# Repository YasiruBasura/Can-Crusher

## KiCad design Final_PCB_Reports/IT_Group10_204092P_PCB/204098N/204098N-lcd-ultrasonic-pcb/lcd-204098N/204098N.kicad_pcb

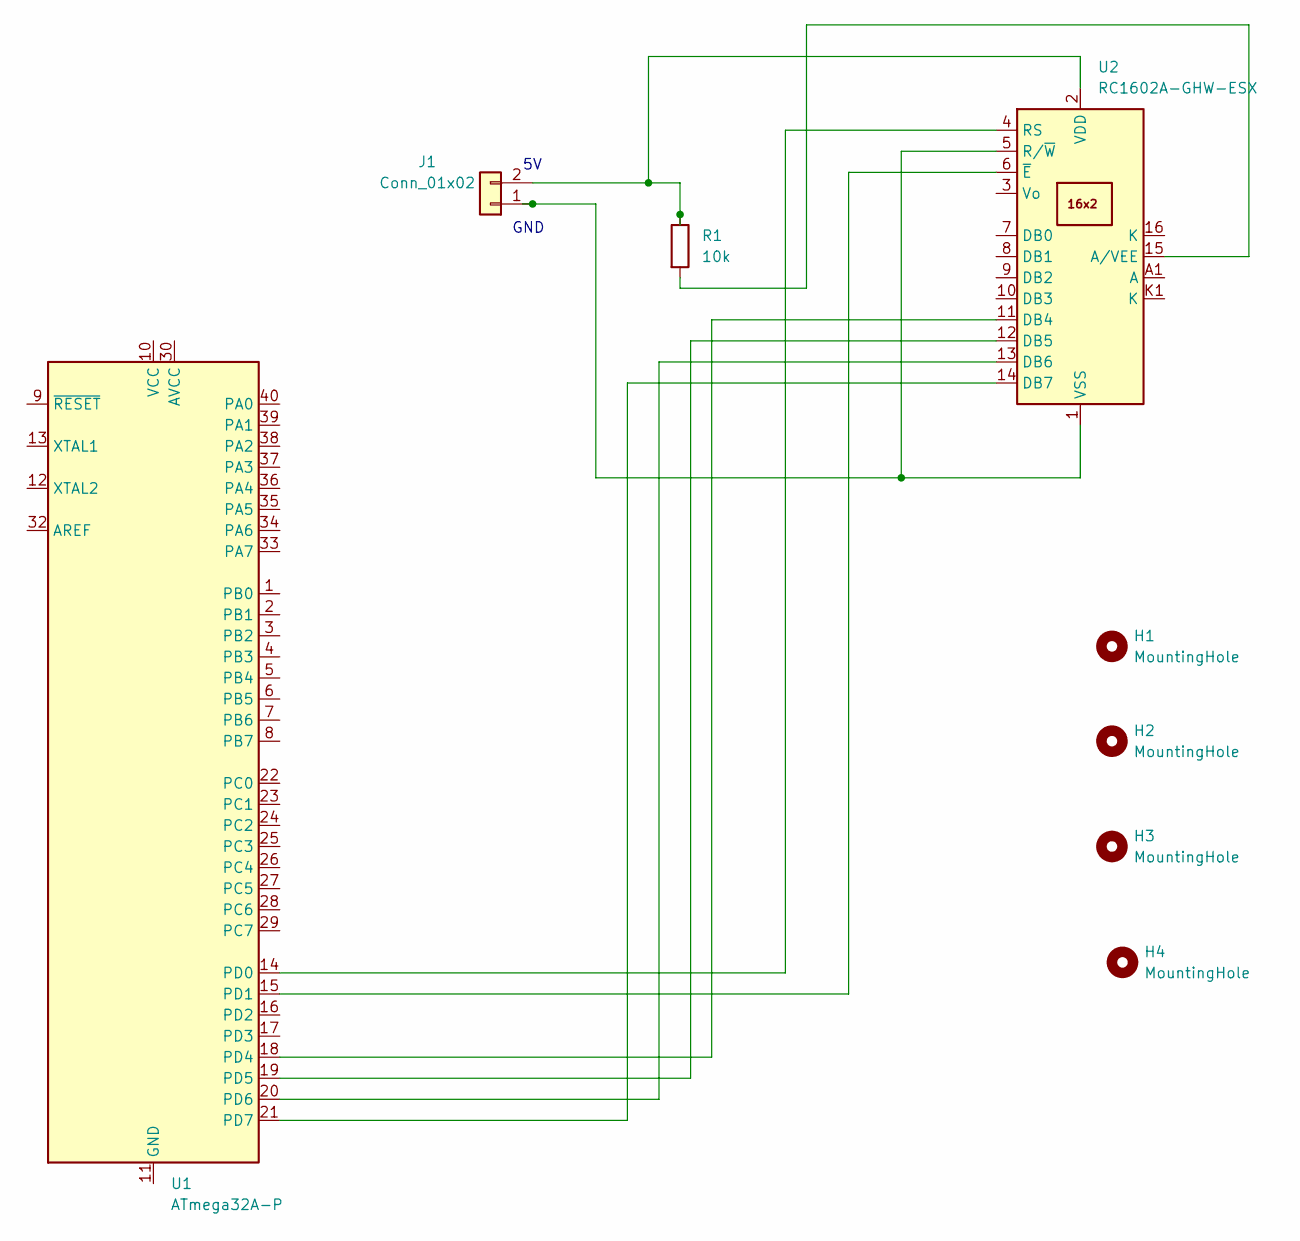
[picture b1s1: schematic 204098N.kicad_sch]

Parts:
H1, H2, H3, H4: MountingHole; MountingHole_4.5mm
J1: Conn_01x02; PinHeader_1x02_P2.54mm_Horizontal
R1: 10k; R_Axial_DIN0207_L6.3mm_D2.5mm_P15.24mm_Horizontal
U1: ATmega32A-P; DIP-40_W15.24mm
U2: RC1602A-GHW-ESX; RC1602A

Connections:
unnamed: J1.2, R1.1, U2.2 (VDD)
unnamed: R1.2, U2.15 (A/VEE)
unnamed: U1.11 (GND), U1.31 (GND)
unnamed: U1.14 (PD0), U2.4 (RS)
unnamed: U1.15 (PD1), U2.6 (~E)
unnamed: U1.18 (PD4), U2.11 (DB4)
unnamed: U1.19 (PD5), U2.12 (DB5)
unnamed: U1.20 (PD6), U2.13 (DB6)
unnamed: U1.21 (PD7), U2.14 (DB7)
unnamed: J1.1, U2.1 (VSS), U2.5 (R/~W)

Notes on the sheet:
GND

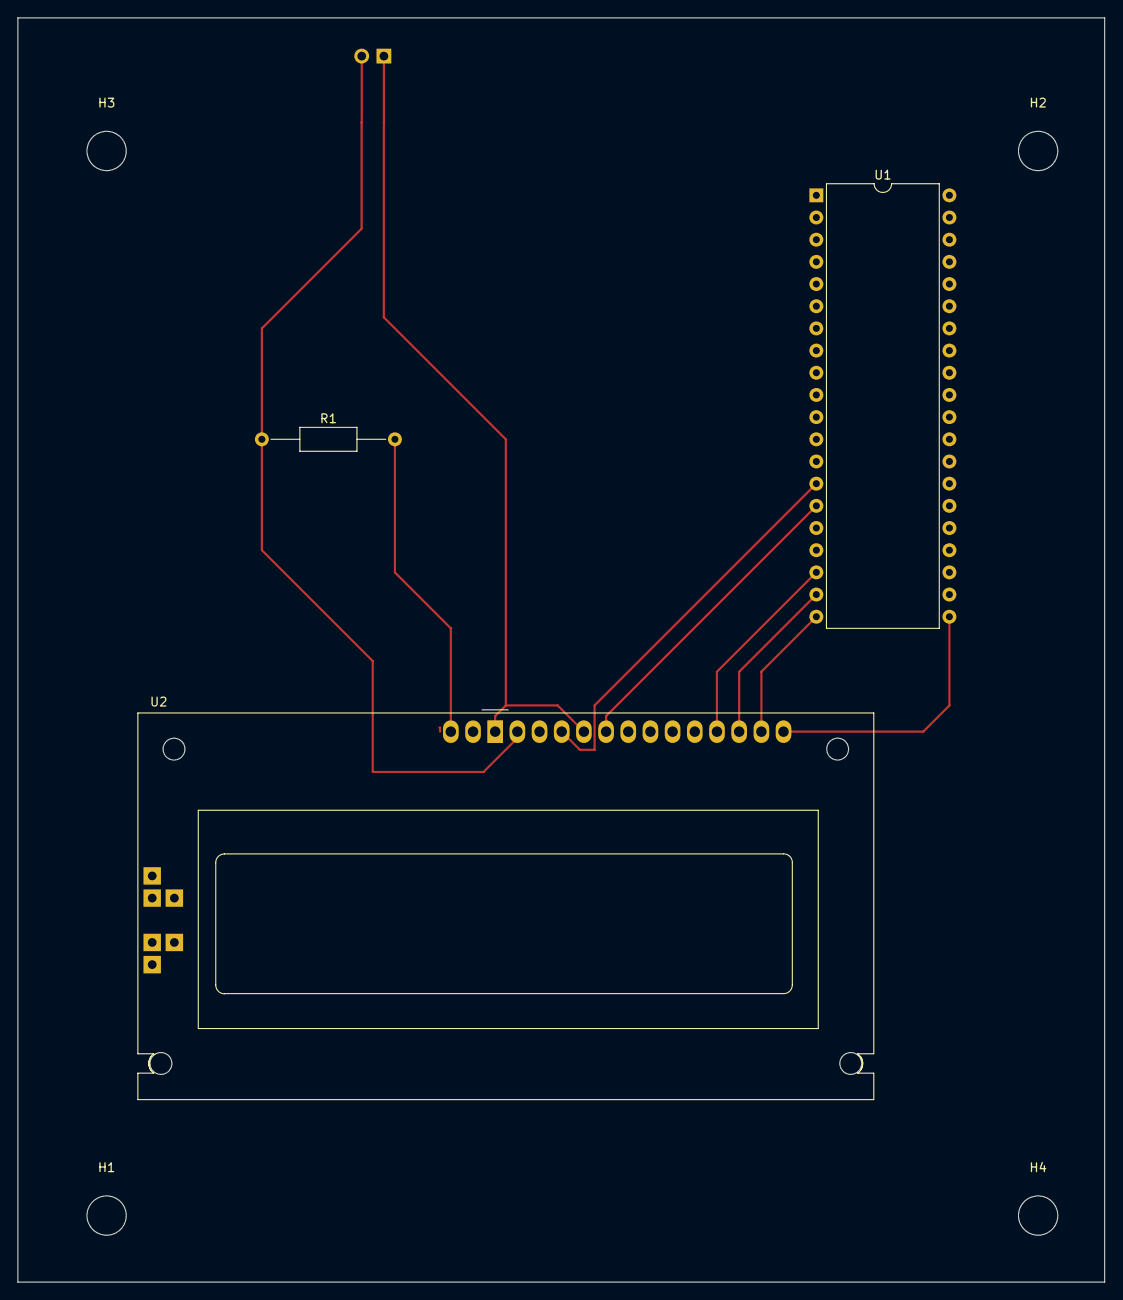
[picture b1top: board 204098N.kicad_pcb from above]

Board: 2 copper layers, 124.5 x 144.8 mm, 8 parts (1 on the bottom side), 10 nets.

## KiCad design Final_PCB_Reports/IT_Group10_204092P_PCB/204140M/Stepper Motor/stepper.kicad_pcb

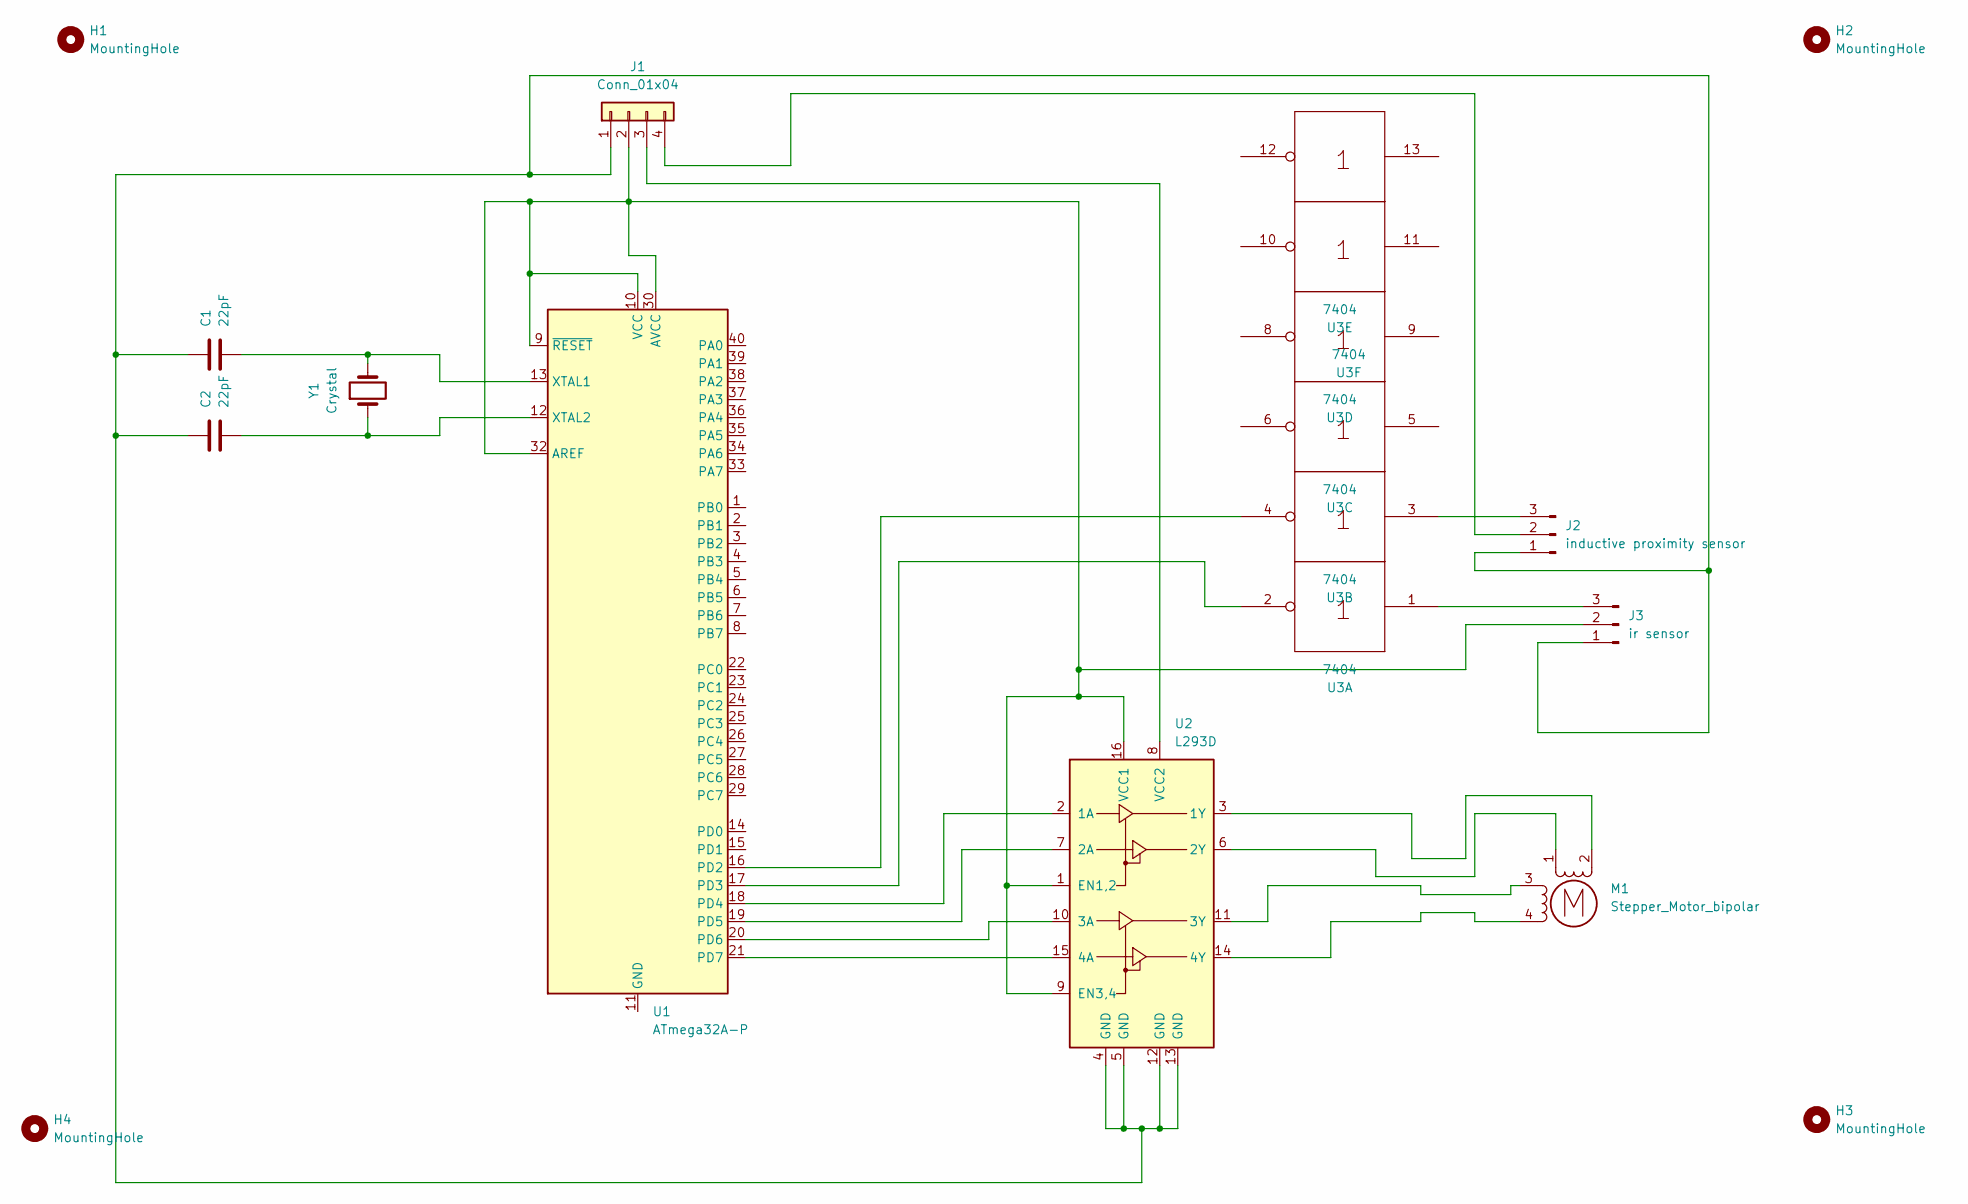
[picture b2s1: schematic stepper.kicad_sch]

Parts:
C1, C2: 22pF; CP_Radial_D4.0mm_P1.50mm
H1, H2, H3, H4: MountingHole; MountingHole_3.5mm_Pad
J1: Conn_01x04; PinHeader_1x04_P2.54mm_Horizontal
J2: inductive proximity sensor; PinSocket_1x03_P1.27mm_Vertical
J3: ir sensor; PinSocket_1x03_P1.27mm_Vertical
M1: Stepper_Motor_bipolar; PinSocket_1x04_P1.27mm_Vertical
U1: ATmega32A-P; DIP-40_W15.24mm
U2: L293D; DIP-16_W7.62mm
U3: 7404; DIP-14_W7.62mm
Y1: Crystal; Crystal_AT310_D3.0mm_L10.0mm_Vertical

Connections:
Gnd: U3.7 (Gnd), U3.14 (Vcc)
unnamed: C1.1, C2.1, J1.1, J2.1, J3.1, U2.4 (GND), U2.5 (GND), U2.12 (GND), U2.13 (GND)
unnamed: C1.2, U1.13 (XTAL1), Y1.2
unnamed: C2.2, U1.12 (XTAL2), Y1.1
unnamed: J1.2, J3.2, U1.9 (~RESET), U1.10 (VCC), U1.30 (AVCC), U1.32 (AREF), U2.1 (EN1,2), U2.9 (EN3,4), U2.16 (VCC1)
unnamed: J1.3, U2.8 (VCC2)
unnamed: J1.4, J2.2
unnamed: J2.3, U3.3
unnamed: J3.3, U3.1
unnamed: M1.1, U2.6 (2Y)
unnamed: M1.2 (-), U2.3 (1Y)
unnamed: M1.3, U2.11 (3Y)
unnamed: M1.4, U2.14 (4Y)
unnamed: U1.11 (GND), U1.31 (GND)
unnamed: U1.16 (PD2), U3.4
unnamed: U1.17 (PD3), U3.2
unnamed: U1.18 (PD4), U2.2 (1A)
unnamed: U1.19 (PD5), U2.7 (2A)
unnamed: U1.20 (PD6), U2.10 (3A)
unnamed: U1.21 (PD7), U2.15 (4A)

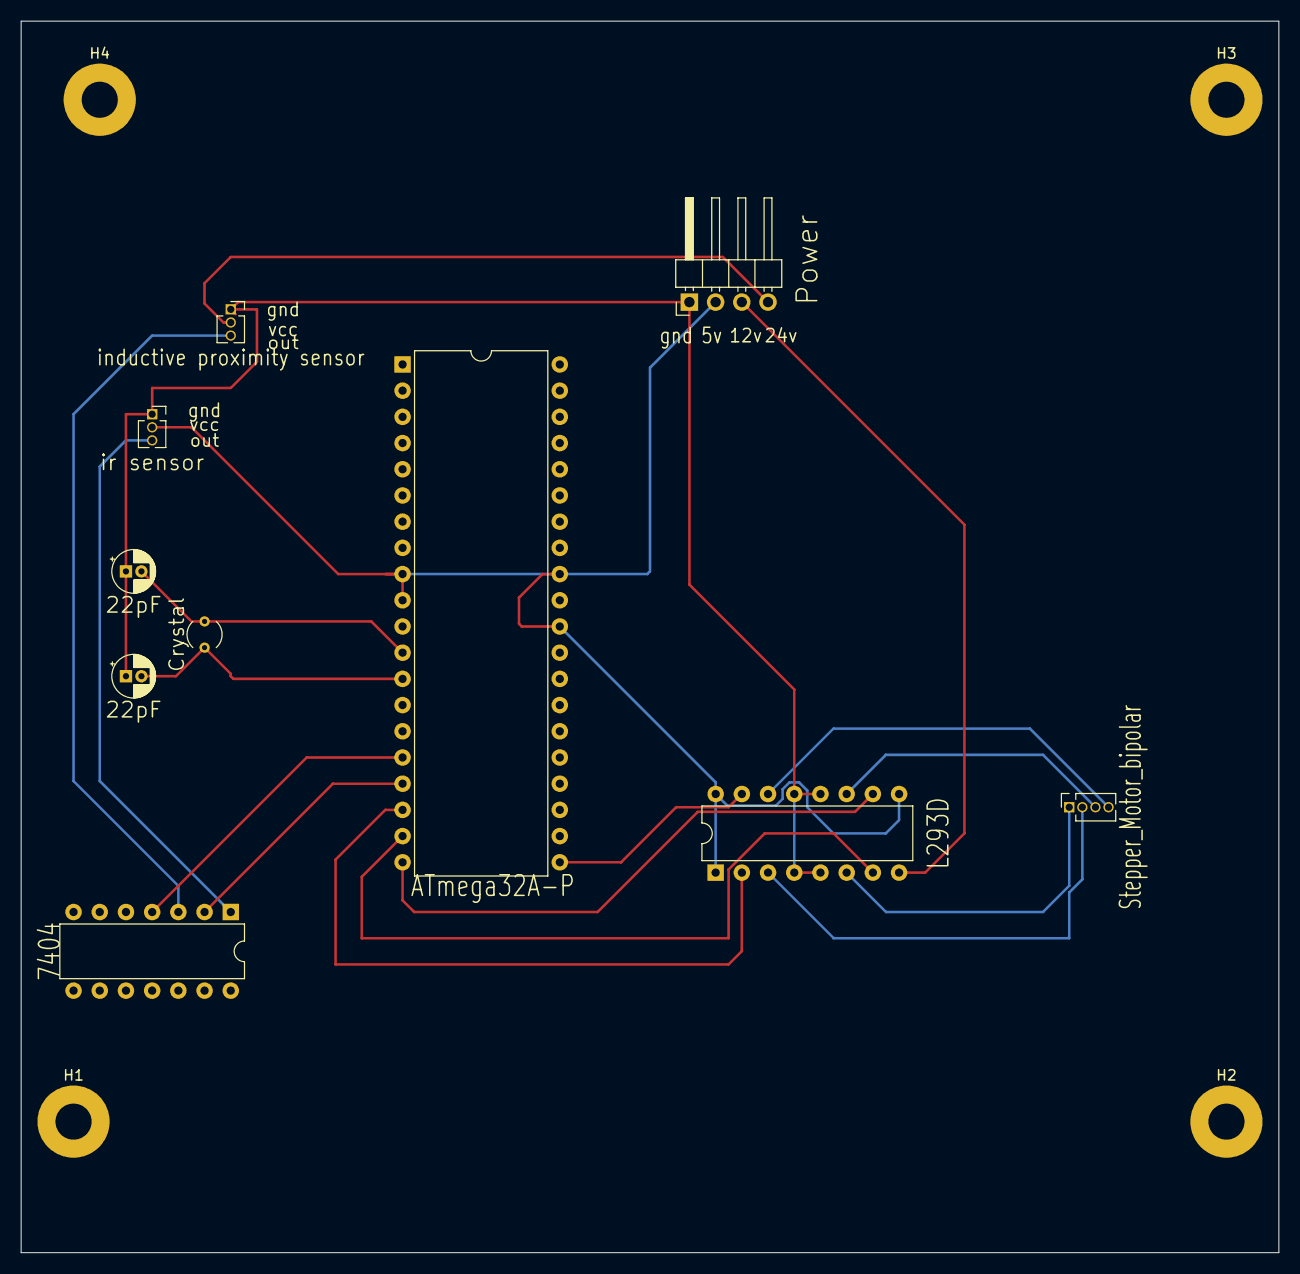
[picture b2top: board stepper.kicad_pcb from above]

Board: 2 copper layers, 121.9 x 119.4 mm, 14 parts (0 on the bottom side), 20 nets.

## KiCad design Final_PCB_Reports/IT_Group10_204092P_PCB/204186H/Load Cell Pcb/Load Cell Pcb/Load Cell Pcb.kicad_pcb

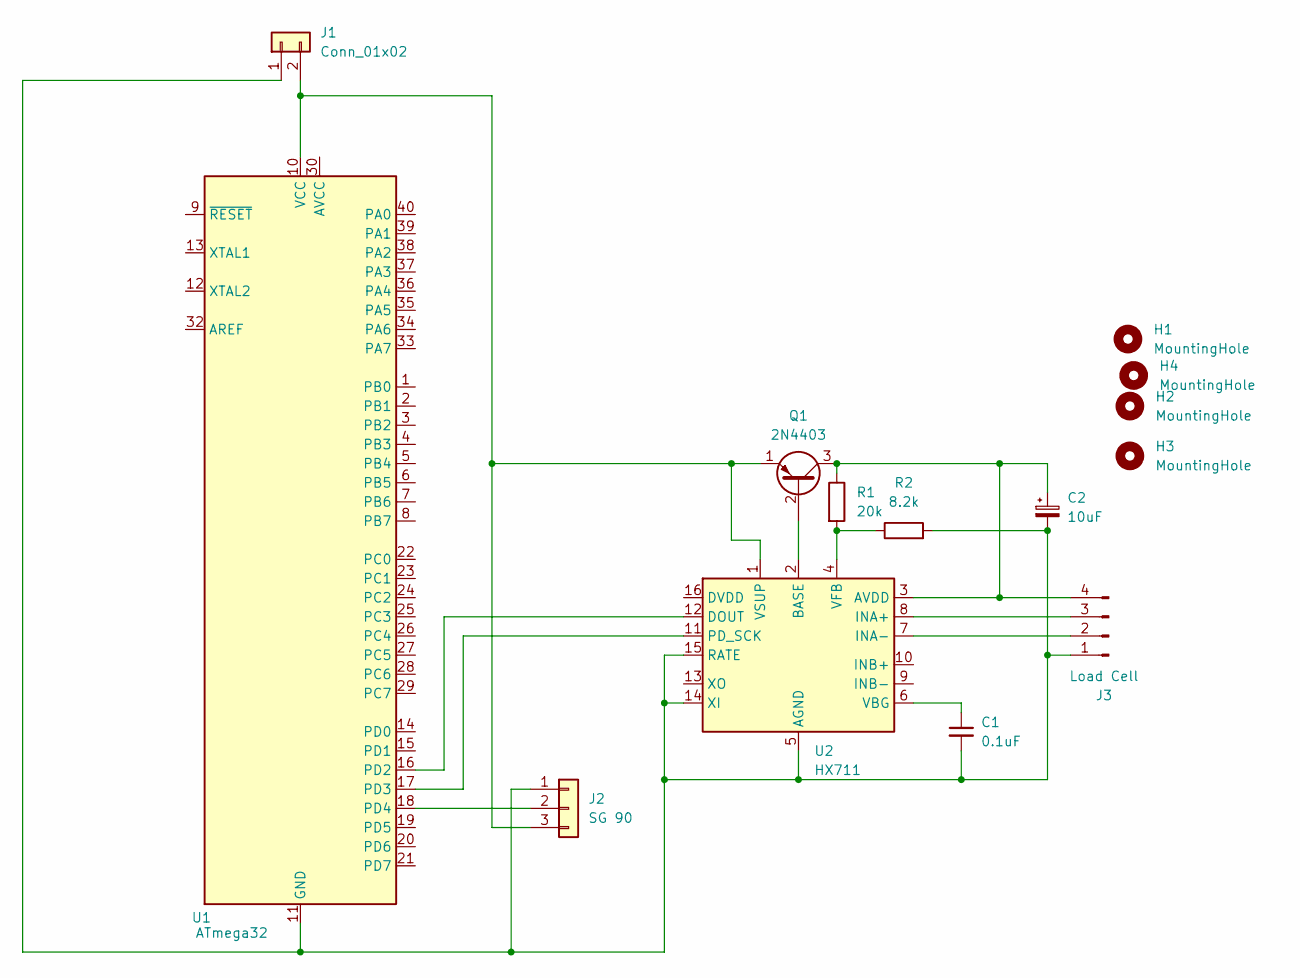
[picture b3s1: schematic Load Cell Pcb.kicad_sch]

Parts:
C1: 0.1uF; CP_Radial_D4.0mm_P2.00mm
C2: 10uF; CP_Radial_D4.0mm_P2.00mm
H1, H2, H3, H4: MountingHole; MountingHole_3.5mm_Pad
J1: Conn_01x02; PinHeader_1x02_P2.54mm_Horizontal
J2: SG 90; PinSocket_1x03_P1.27mm_Vertical
J3: Load Cell; PinSocket_1x04_P1.27mm_Vertical
Q1: 2N4403; TO-92_Inline
R1: 20k; R_Axial_DIN0204_L3.6mm_D1.6mm_P5.08mm_Horizontal
R2: 8.2k; R_Axial_DIN0204_L3.6mm_D1.6mm_P5.08mm_Vertical
U1: ATmega32; DIP-40_W15.24mm
U2: HX711; DIP-14_W7.62mm

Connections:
unnamed: C1.1, U2.6 (VBG)
unnamed: C1.2, C2.2, J1.1, J2.1, J3.1, R2.2, U1.11 (GND), U1.31 (GND), U2.5 (AGND), U2.14 (XI), U2.15 (RATE)
unnamed: C2.1, J3.4, Q1.3 (C), R1.1, U2.3 (AVDD)
unnamed: J2.2, U1.18 (PD4)
unnamed: J1.2, J2.3, Q1.1 (E), U1.10 (VCC), U2.1 (VSUP)
unnamed: J3.2, U2.7 (INA-)
unnamed: J3.3, U2.8 (INA+)
unnamed: Q1.2 (B), U2.2 (BASE)
unnamed: R1.2, R2.1, U2.4 (VFB)
unnamed: U1.16 (PD2), U2.12 (DOUT)
unnamed: U1.17 (PD3), U2.11 (PD_SCK)

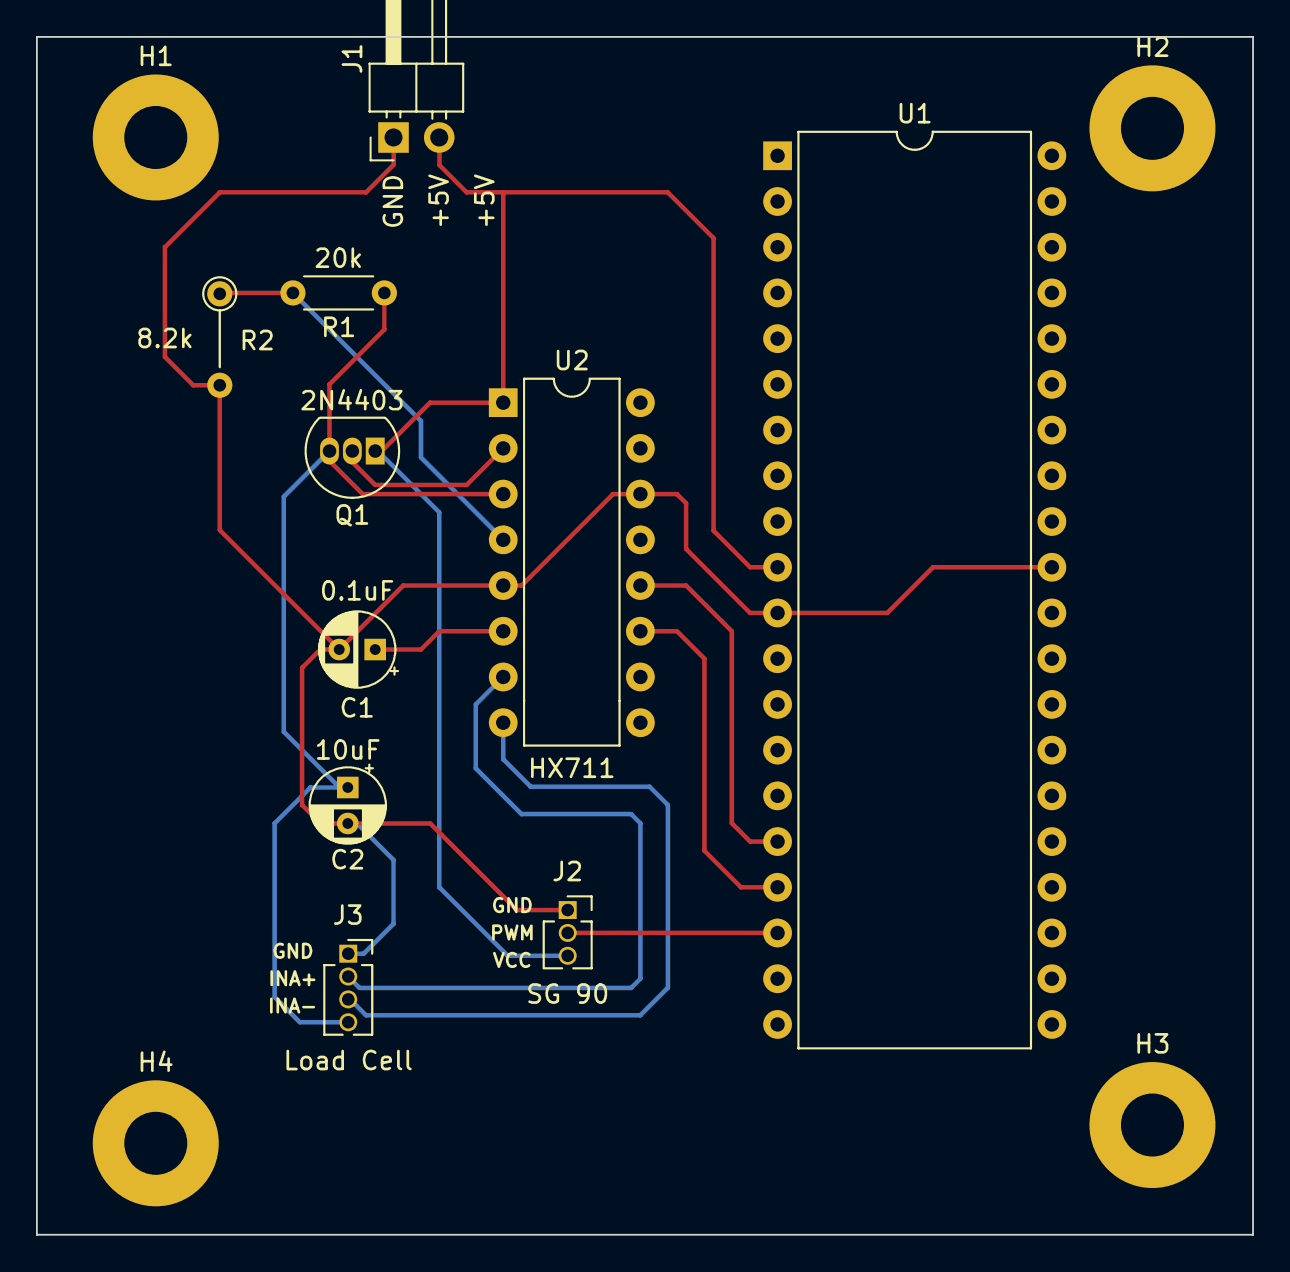
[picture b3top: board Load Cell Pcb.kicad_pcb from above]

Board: 2 copper layers, 67.6 x 66.5 mm, 14 parts (0 on the bottom side), 11 nets.
